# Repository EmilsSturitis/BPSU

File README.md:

# BPSU
Bipolar power supply board, for op-amp's and other things

from input +5VD to +/-12VDC, with additional LDO'S for: +/-1.8V, +/-2.5V, +/-3.3V, +/-5V.

IC's used ADP5070, ADP7142 and ADP7182

 |

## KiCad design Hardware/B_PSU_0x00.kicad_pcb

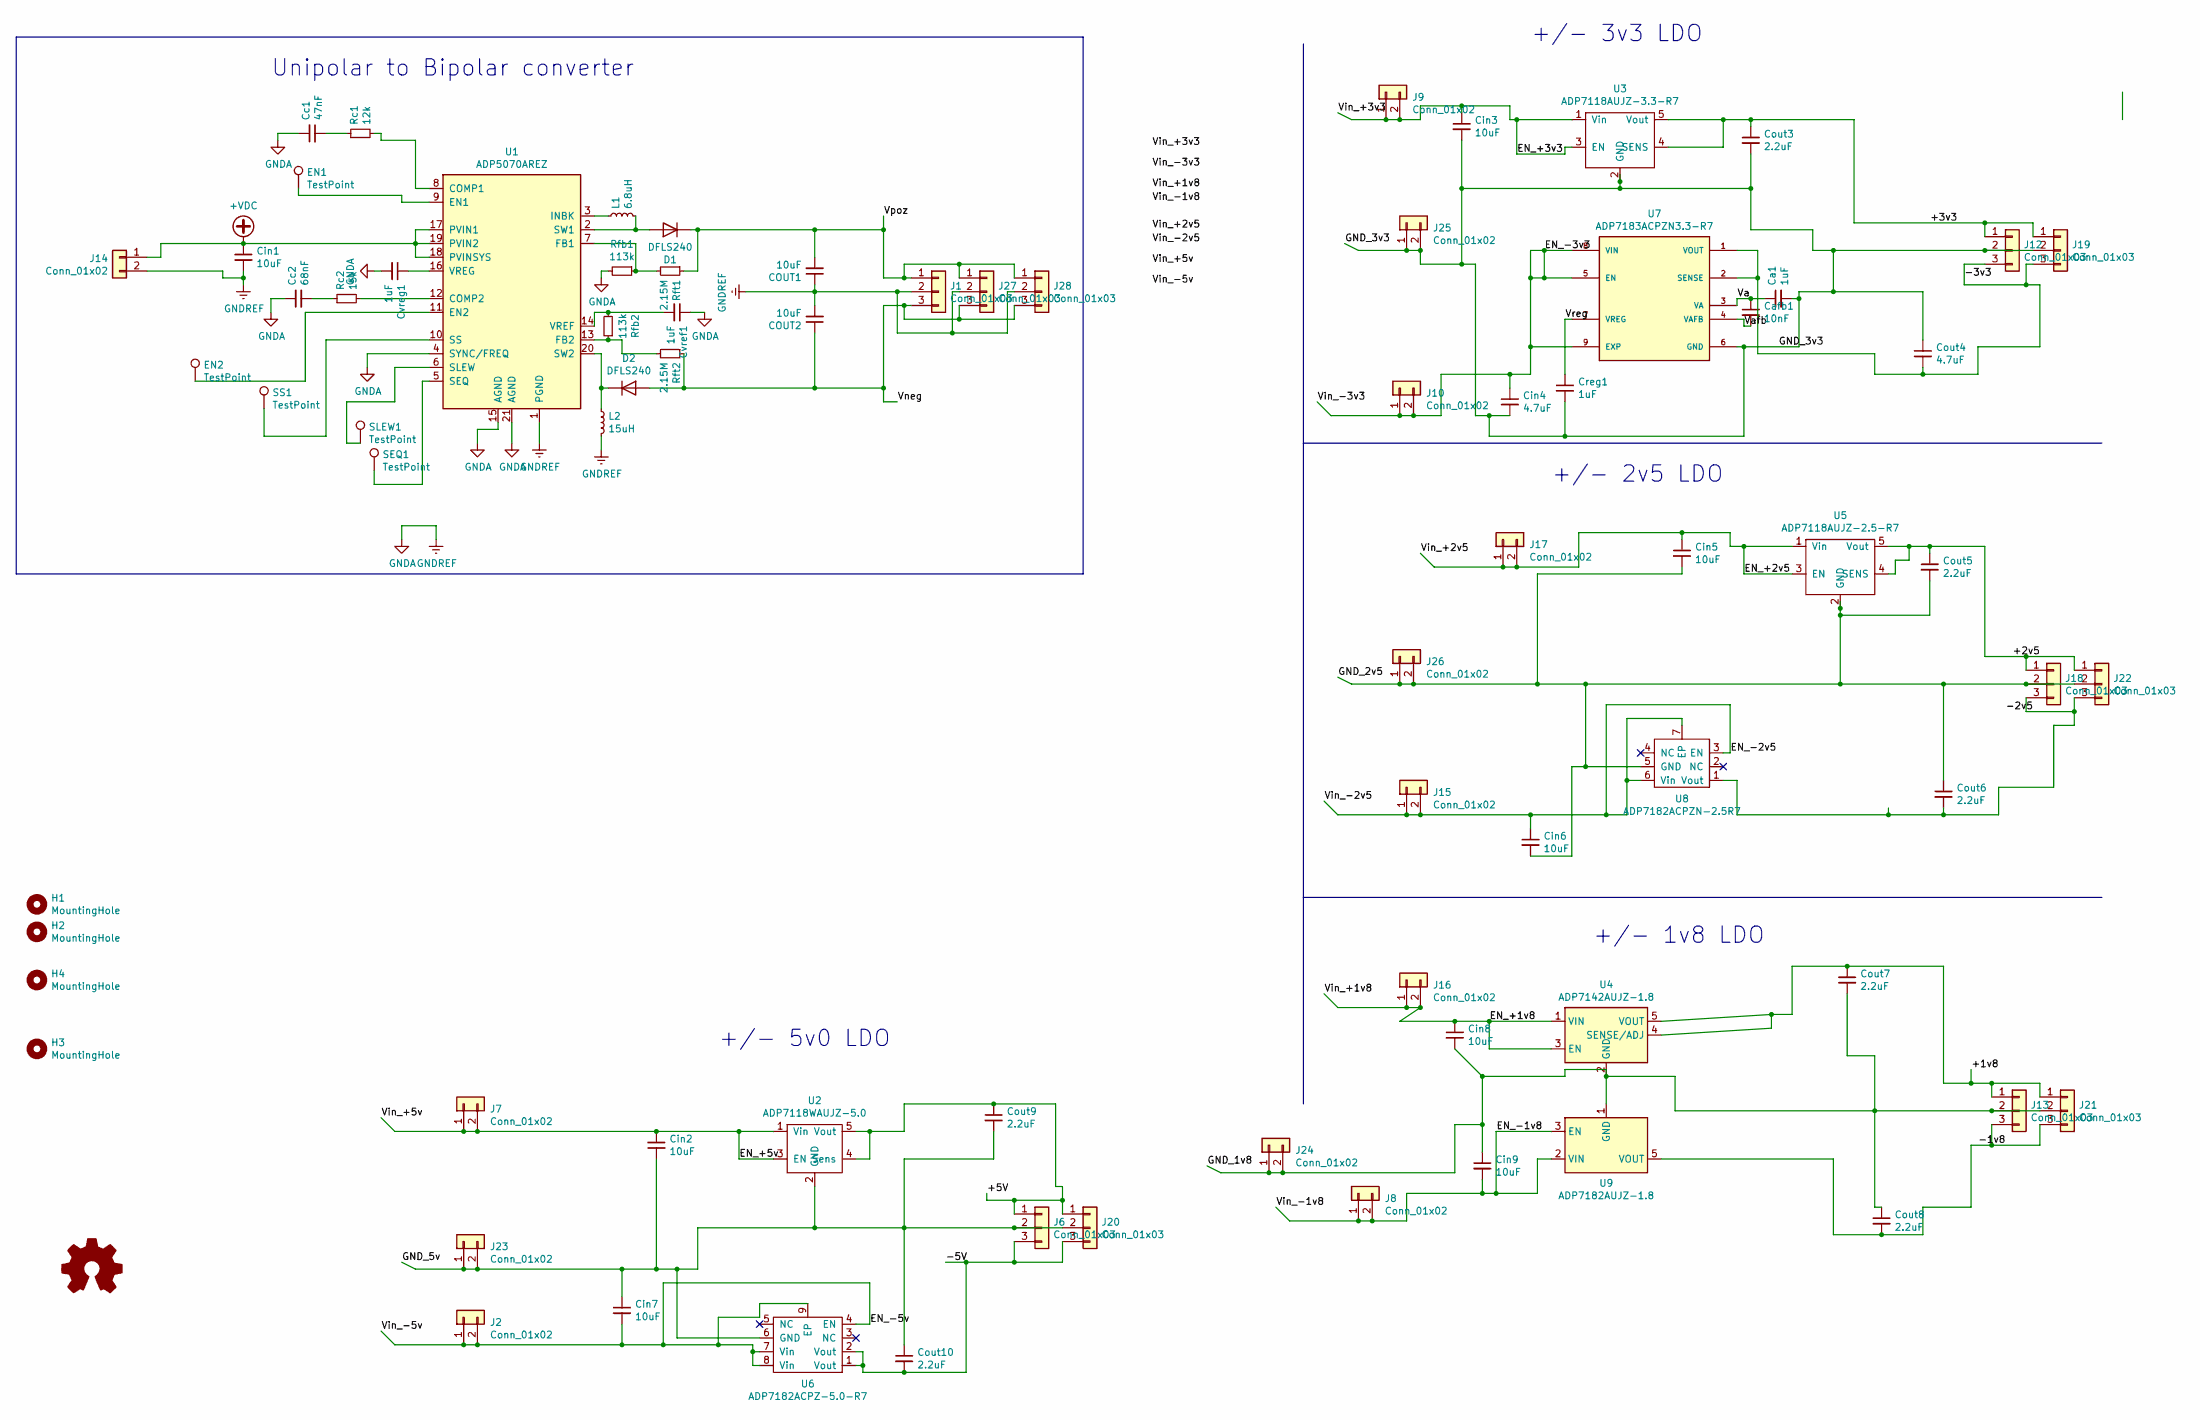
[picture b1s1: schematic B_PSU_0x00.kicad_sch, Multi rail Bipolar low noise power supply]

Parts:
COUT1, COUT2: 10uF; C_1210_3225Metric_Pad1.33x2.70mm_HandSolder
Ca1: 1uF; C_1206_3216Metric_Pad1.33x1.80mm_HandSolder
Cafb1: 10nF; C_1206_3216Metric_Pad1.33x1.80mm_HandSolder
Cc1: 47nF; C_0805_2012Metric_Pad1.18x1.45mm_HandSolder
Cc2: 68nF; C_0805_2012Metric_Pad1.18x1.45mm_HandSolder
Cin1, Cin2, Cin3, Cin5, Cin6, Cin7, Cin8, Cin9: 10uF; C_1206_3216Metric_Pad1.33x1.80mm_HandSolder
Cin4: 4.7uF; C_1206_3216Metric_Pad1.33x1.80mm_HandSolder
Cout3, Cout5, Cout6, Cout7, Cout8, Cout9, Cout10: 2.2uF; C_1206_3216Metric_Pad1.33x1.80mm_HandSolder
Cout4: 4.7uF; C_1206_3216Metric_Pad1.33x1.80mm_HandSolder
Creg1: 1uF; C_1206_3216Metric_Pad1.33x1.80mm_HandSolder
Cvref1: 1uF; C_0805_2012Metric_Pad1.18x1.45mm_HandSolder
Cvreg1: 1uF; C_0805_2012Metric_Pad1.18x1.45mm_HandSolder
D1, D2: DFLS240; D_SOD-123F
EN1, EN2: TestPoint; TestPoint_Pad_D2.5mm
H1, H2, H3, H4: MountingHole; MountingHole_3.2mm_M3
J1, J6, J12, J13, J18, J19, J20, J21, J22, J27, J28: Conn_01x03; PinHeader_1x03_P2.54mm_Vertical
J2, J7, J8, J9, J10, J15, J16, J17, J23, J24, J25, J26: Conn_01x02; PinHeader_1x02_P2.54mm_Vertical
J14: Conn_01x02; TerminalBlock_bornier-2_P5.08mm
L1: 6.8uH; L_Coilcraft_XxL4040
L2: 15uH; L_Coilcraft_XxL4030
Rc1: 12k; R_0805_2012Metric_Pad1.20x1.40mm_HandSolder
Rc2: 15k; R_0805_2012Metric_Pad1.20x1.40mm_HandSolder
Rfb1, Rfb2: 113k; R_0805_2012Metric_Pad1.20x1.40mm_HandSolder
Rft1, Rft2: 2.15M; R_0805_2012Metric_Pad1.20x1.40mm_HandSolder
SEQ1: TestPoint; TestPoint_Pad_D2.5mm
SLEW1: TestPoint; TestPoint_Pad_D2.5mm
SS1: TestPoint; TestPoint_Pad_D2.5mm
U1: ADP5070AREZ; ETSSOP-20-1EP_4.4x6.5mm_P0.65mm_EP3x4.2mm
U2: ADP7118WAUJZ-5.0; TSOT-23-5_HandSoldering
U3: ADP7118AUJZ-3.3-R7; TSOT-23-5_HandSoldering
U4: ADP7142AUJZ-1.8; TSOT-23-5
U5: ADP7118AUJZ-2.5-R7; TSOT-23-5_HandSoldering
U6: ADP7182ACPZ-5.0-R7; LFCSP-8-1EP_3x3mm_P0.5mm_EP1.45x1.74mm
U7: ADP7183ACPZN3.3-R7; SON50P200X200X60-9N
U8: ADP7182ACPZN-2.5R7; DFN-6-1EP_2x2mm_P0.65mm_EP1x1.6mm
U9: ADP7182AUJZ-1.8; TSOT-23-5

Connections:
+VDC: Cin1.1, J14.1, U1.17 (PVIN1), U1.18 (PVINSYS), U1.19 (PVIN2)
/+1v8: Cout7.1, J13.1, J21.1, U4.4 (SENSE/ADJ), U4.5 (VOUT)
/+2v5: Cout5.1, J18.1, J22.1, U5.4 (SENS), U5.5 (Vout)
/+3v3: Cout3.1, J12.1, J19.1, U3.4 (SENS), U3.5 (Vout)
/+5V: Cout9.1, J6.1, J20.1, U2.4 (Sens), U2.5 (Vout)
/-1v8: Cout8.2, J13.3, J21.3, U9.5 (VOUT)
/-3v3: Cout4.2, J12.3, J19.3, U7.1 (VOUT), U7.2 (SENSE)
/-5V: Cout10.2, J6.3, J20.3, U6.1 (Vout), U6.2 (Vout)
/EN_+1v8: Cin8.1, J16.1, J16.2, U4.1 (VIN), U4.3 (EN)
/EN_+2v5: Cin5.1, J17.1, J17.2, U5.1 (Vin), U5.3 (EN)
/EN_+3v3: Cin3.1, J9.1, J9.2, U3.1 (Vin), U3.3 (EN)
/EN_+5v: Cin2.1, J7.1, J7.2, U2.1 (Vin), U2.3 (EN)
/EN_-1v8: Cin9.2, J8.1, J8.2, U9.2 (VIN), U9.3 (EN)
/EN_-2v5: Cin6.1, J15.1, J15.2, U8.3 (EN), U8.6 (Vin), U8.7 (EP)
/EN_-3v3: Cin4.1, J10.1, J10.2, U7.5 (EN), U7.8 (VIN), U7.9 (EXP)
/EN_-5v: Cin7.2, J2.1, J2.2, U6.4 (EN), U6.7 (Vin), U6.8 (Vin), U6.9 (EP)
/GND_1v8: Cin8.2, Cin9.1, Cout7.2, Cout8.1, J13.2, J21.2, J24.1, J24.2, U4.2 (GND), U9.1 (GND)
/GND_2v5: Cin5.2, Cin6.2, Cout5.2, Cout6.1, J18.2, J22.2, J26.1, J26.2, U5.2 (GND), U8.5 (GND)
/GND_3v3: Ca1.2, Cin3.2, Cin4.2, Cout3.2, Cout4.1, Creg1.2, J12.2, J19.2, J25.1, J25.2, U3.2 (GND), U7.6 (GND)
/GND_5v: Cin2.2, Cin7.1, Cout9.2, Cout10.1, J6.2, J20.2, J23.1, J23.2, U2.2 (GND), U6.6 (GND)
/Va: Ca1.1, Cafb1.1, U7.3 (VA)
/Vafb: Cafb1.2, U7.4 (VAFB)
/Vneg: COUT2.1, D2.2 (A), J1.3, J27.3, J28.3, Rft2.1
/Vpoz: COUT1.2, D1.1 (K), J1.1, J27.1, J28.1, Rft1.1
/Vreg: Creg1.1, U7.7 (VREG)
GNDA: COUT1.1, COUT2.2, Cc1.1, Cc2.1, Cin1.2, Cvref1.1, Cvreg1.2, J1.2, J14.2, J27.2, J28.2, L2.2, Rfb1.2, U1.1 (PGND), U1.4 (SYNC/FREQ), U1.15 (AGND), U1.21 (AGND)
unnamed: Cc1.2, Rc1.1
unnamed: Cc2.2, Rc2.1
unnamed: D1.2 (A), L1.2, U1.2 (SW1)
unnamed: D2.1 (K), L2.1, U1.20 (SW2)
unnamed: Cout6.2, J18.3, J22.3, U8.1 (Vout)
unnamed: Rc1.2, U1.8 (COMP1)
unnamed: Rc2.2, U1.12 (COMP2)
unnamed: EN1.1, U1.9 (EN1)
unnamed: EN2.1, U1.11 (EN2)
unnamed: Rfb1.1, Rft1.2, U1.7 (FB1)
unnamed: Rfb2.1, Rft2.2, U1.13 (FB2)
unnamed: L1.1, U1.3 (INBK)
unnamed: SEQ1.1, U1.5 (SEQ)
unnamed: SLEW1.1, U1.6 (SLEW)
unnamed: SS1.1, U1.10 (SS)
unnamed: Cvref1.2, Rfb2.2, U1.14 (VREF)
unnamed: Cvreg1.1, U1.16 (VREG)

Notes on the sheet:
+/- 5v0 LDO
Unipolar to Bipolar converter
+/- 2v5 LDO
+/- 1v8 LDO
+/- 3v3 LDO

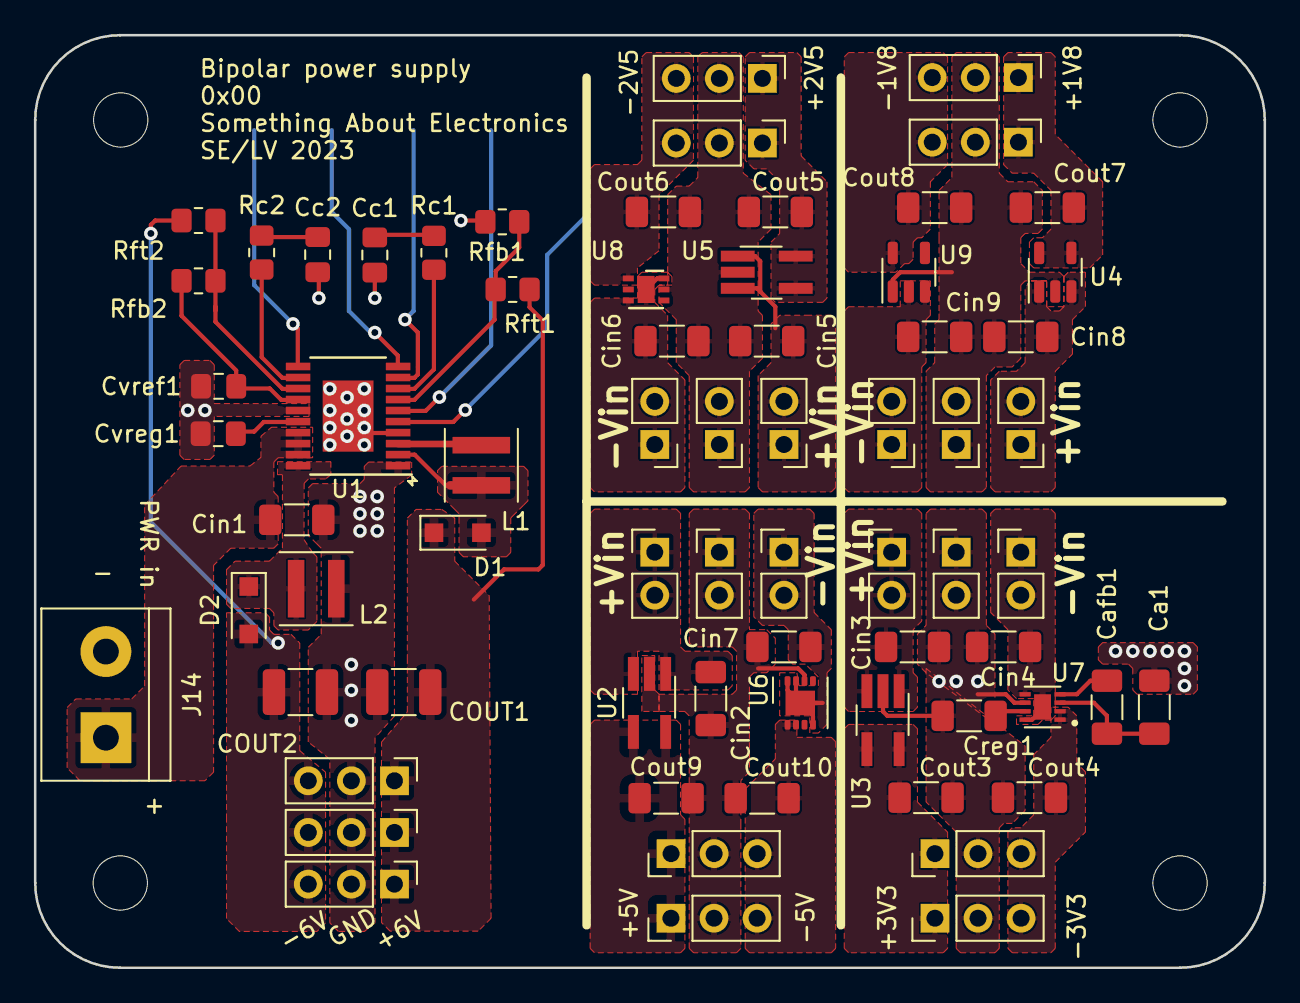
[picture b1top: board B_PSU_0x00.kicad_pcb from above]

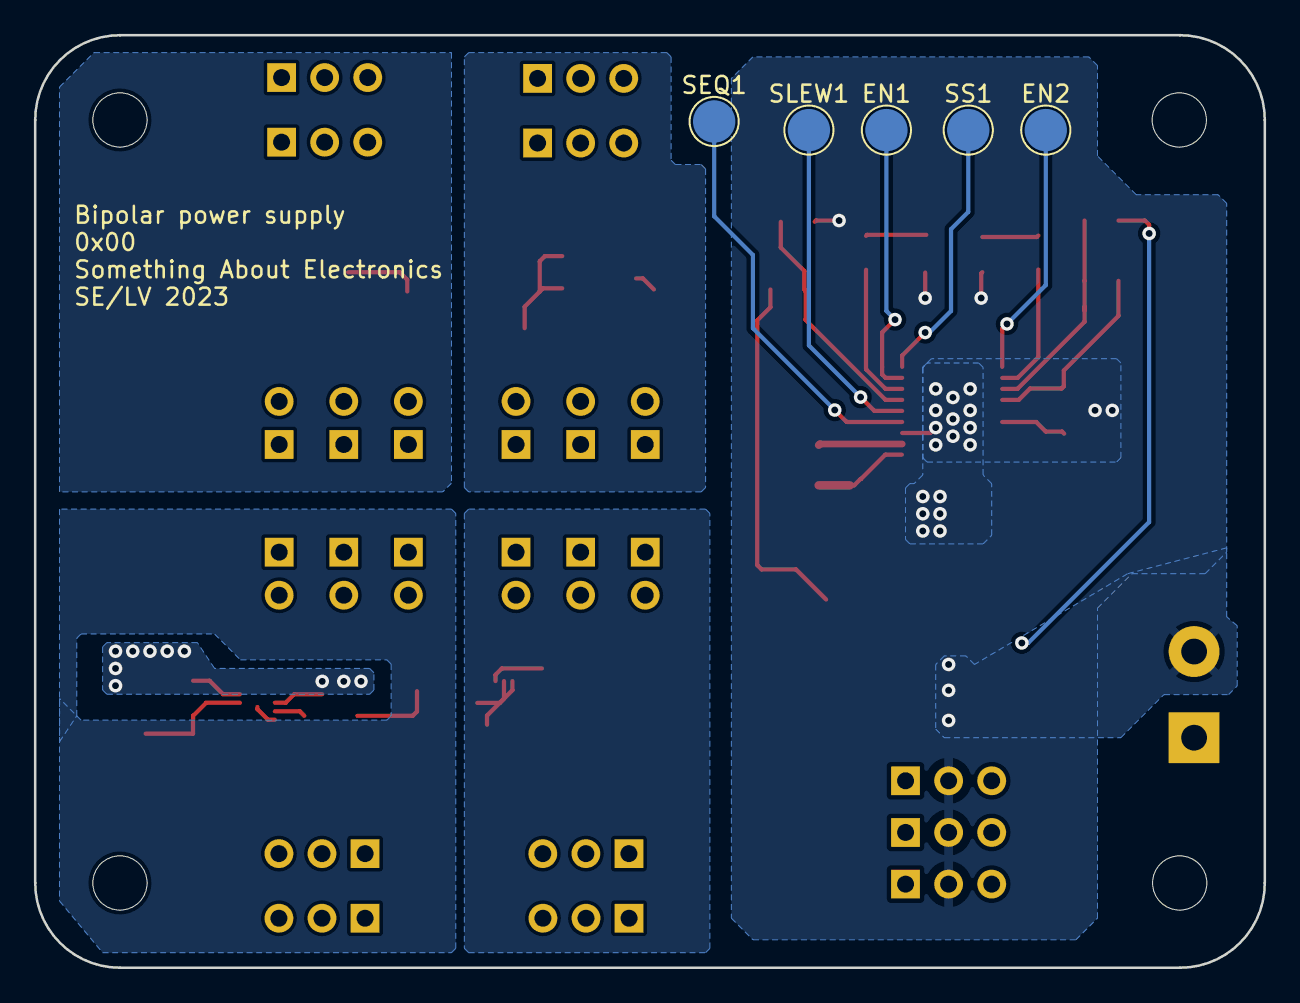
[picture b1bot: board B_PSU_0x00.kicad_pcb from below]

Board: 2 copper layers, 72.5 x 55.0 mm, 78 parts (5 on the bottom side), 43 nets.

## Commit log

2022-06-27 Update B_PSU_0x00.sch
    Changed number of ADP5070 converters from two to one
2022-06-29 LDO's changed to the ones you can buy
2022-07-30 updated to sch and pcb
    correct LDO ic's and board outline
2023-01-01 cleaned up layout
2023-01-09 changed the layout and the size of the PCB
2023-01-20 small updates
2023-03-03 0x00 version and revision files for manufacturing
2025-07-17 update to readme
